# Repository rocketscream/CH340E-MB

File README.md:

# CH340E-MB
CH340E USB-Serial Adapter

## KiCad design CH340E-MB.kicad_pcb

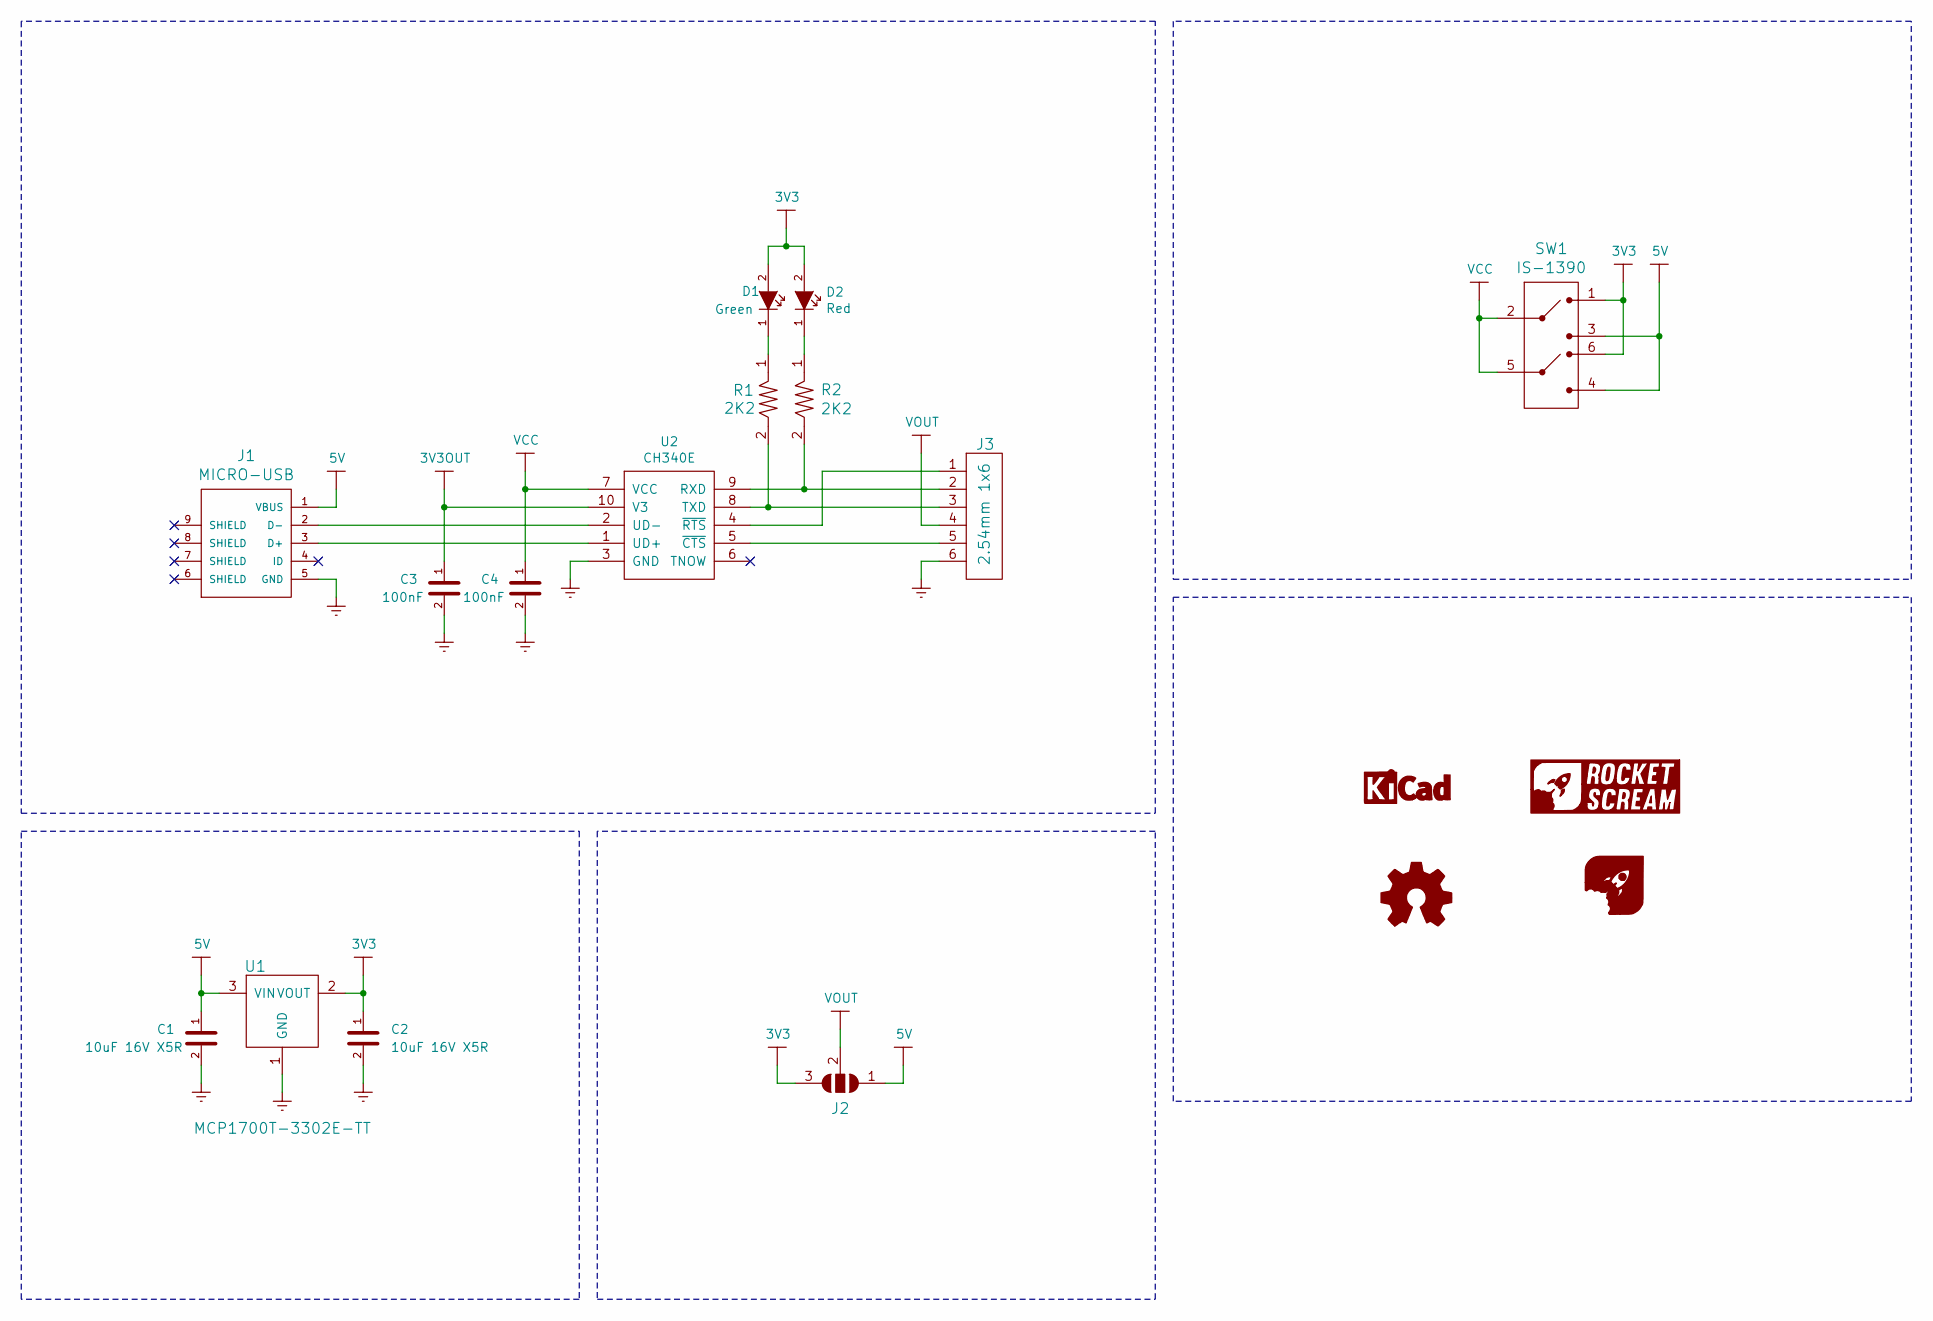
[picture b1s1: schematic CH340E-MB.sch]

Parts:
C1, C2: 10uF 16V X5R; C_0603
C3, C4: 100nF; C_0603
D1: Green; LED_0603
D2: Red; LED_0603
J1: MICRO-USB
J2: JUMPER-2-WAY; JUMPER-2-WAY-SMD
J3: 2.54mm 1x6; RCP_1x6_Pitch2.54mm_RightAngle
LOGO1: LOGO-OSHW; LOGO-OSHW_XSmall
LOGO2: LOGO-ROCKET-SCREAM-HORIZONTAL; LOGO-ROCKET-SCREAM_Horizontal_XXSmall
LOGO3: LOGO-ROCKET-SCREAM-WITHOUT-TEXT; LOGO-ROCKET-SCREAM_Without_Text_XXXXSmall
LOGO4: LOGO-KICAD; LOGO-KICAD_XXXSmall
R1, R2: 2K2; R_0603
SW1: IS-1390
U1: MCP1700T-3302E-TT; SOT-23
U2: CH340E; MSOP-10

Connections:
3V3: C2.1, D1.2 (A), D2.2 (A), J2.3, SW1.1, SW1.6, U1.2 (VOUT)
3V3OUT: C3.1, U2.10 (V3)
5V: C1.1, J1.1 (VBUS), J2.1, SW1.3, SW1.4, U1.3 (VIN)
GND: C1.2, C2.2, C3.2, C4.2, J1.5 (GND), J3.6, U1.1 (GND), U2.3 (GND)
unnamed: D1.1 (K), R1.1
unnamed: D2.1 (K), R2.1
unnamed: J1.2 (D-), U2.2 (UD-)
unnamed: J1.3 (D+), U2.1 (UD+)
unnamed: J3.1, U2.4 (~RTS~)
unnamed: J3.2, R2.2, U2.9 (RXD)
unnamed: J3.3, R1.2, U2.8 (TXD)
unnamed: J3.5, U2.5 (~CTS~)
VCC: C4.1, SW1.2, SW1.5, U2.7 (VCC)
VOUT: J2.2, J3.4

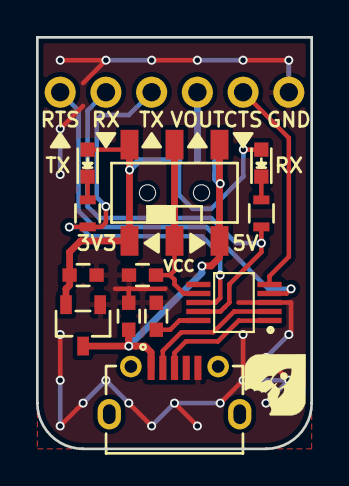
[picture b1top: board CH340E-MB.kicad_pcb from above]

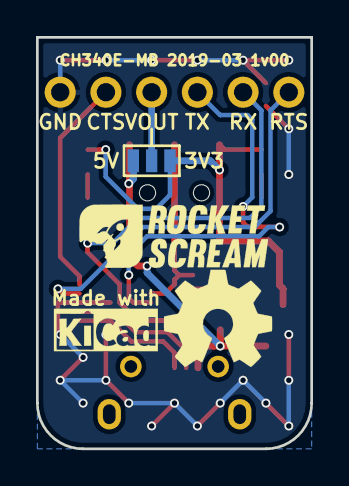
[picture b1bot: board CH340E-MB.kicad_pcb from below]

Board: 2 copper layers, 15.2 x 22.9 mm, 18 parts (4 on the bottom side), 14 nets.

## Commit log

2019-04-18 v1.00
